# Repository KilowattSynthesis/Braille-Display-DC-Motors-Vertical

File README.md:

# Braille-Display-DC-Motors-Vertical

Braille display POC using 0408 DC motors, vertically inline under each dot, to spin a bolt for each dot. Includes CAD, PCB, and Firmware. 

**Type 5:** Vertical DC motors.

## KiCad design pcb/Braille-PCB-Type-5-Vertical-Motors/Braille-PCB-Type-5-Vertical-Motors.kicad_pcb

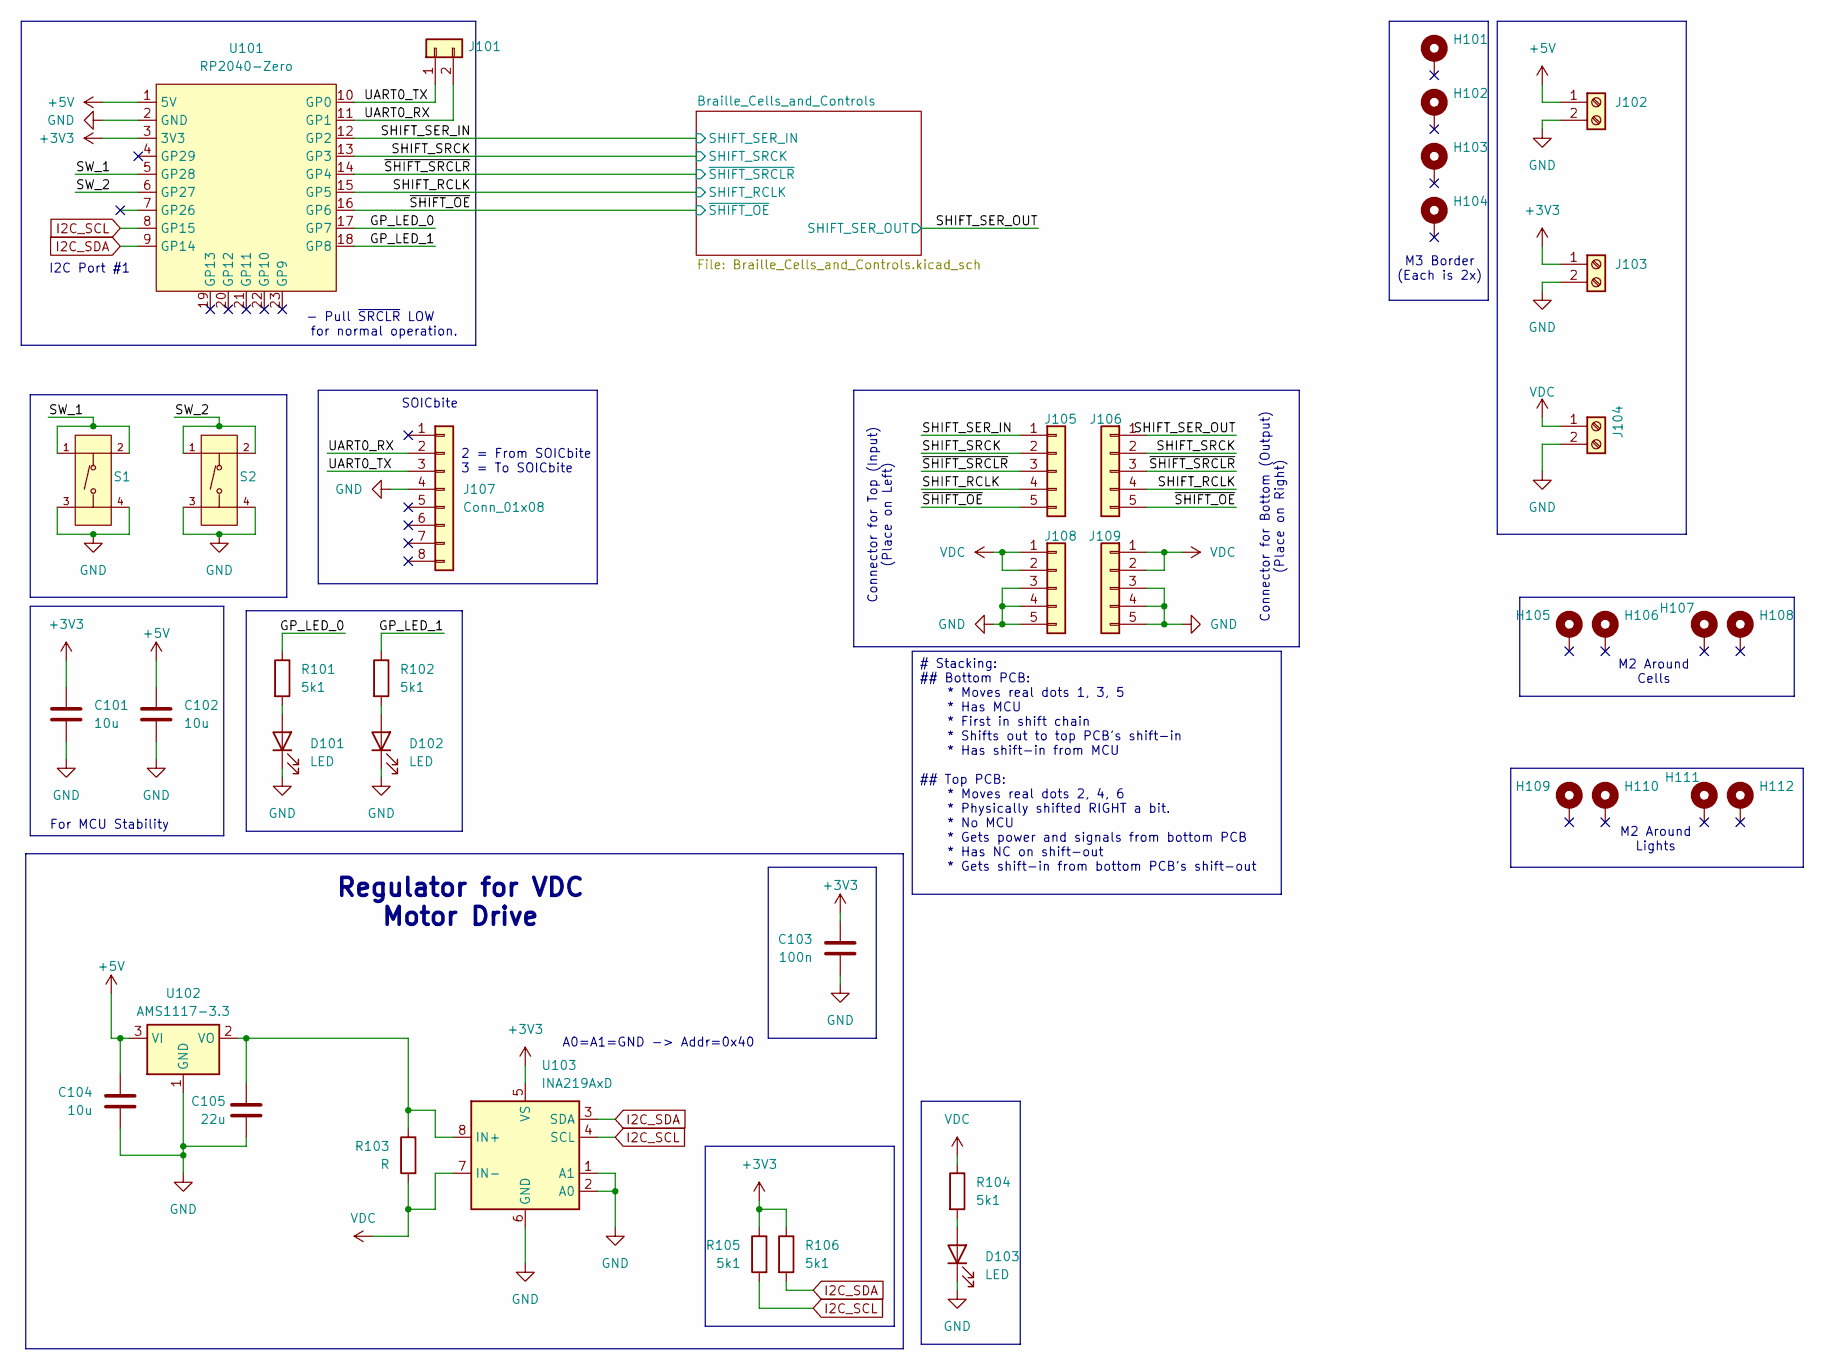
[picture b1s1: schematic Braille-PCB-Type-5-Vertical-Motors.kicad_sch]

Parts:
C101, C102, C104: 10u; C_1206_3216Metric_Pad1.33x1.80mm_HandSolder
C103: 100n; C_0603_1608Metric_Pad1.08x0.95mm_HandSolder
C105: 22u; C_1206_3216Metric_Pad1.33x1.80mm_HandSolder
D101, D102, D103: LED; LED_0603_1608Metric_Pad1.05x0.95mm_HandSolder
H101, H102, H103, H104: MountingHole_Pad; MountingHole_M3_2x_3mm_Pitch
H105, H106, H107, H108, H109, H110, H111, H112: MountingHole_Pad; Braille_Block_MountingHoles_M2_3x
J101: Conn_01x02; PinHeader_1x02_P2.54mm_Vertical
J102, J103, J104: Screw_Terminal_01x02; TerminalBlock_bornier-2_P5.08mm
J105, J106, J108, J109: Conn_01x05; PinHeader_1x05_P2.54mm_Vertical_Tight_Centered
J107: Conn_01x08; SOICbite_clipProgSmall
R101, R102, R104, R105, R106: 5k1; R_0603_1608Metric_Pad0.98x0.95mm_HandSolder
R103: R; R_1206_3216Metric_Pad1.30x1.75mm_HandSolder
S1, S2: Tactile Button, 160gf; SW-SMD_4P-L5.1-W5.1-P3.70-LS6.5-TL-2; Voltage Rating (Dc) 12V; Part TS-1187A-B-A-B; LCSC C318884
U101: RP2040-Zero; RP2040 Zero
U102: AMS1117-3.3; SOT-223-3_TabPin2
U103: INA219AxD; SOIC-8_3.9x4.9mm_P1.27mm

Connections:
+3V3: C101.1, C103.1, J103.1, R105.1, R106.1, U101.3 (3V3), U103.5 (VS); also elsewhere on the board
+5V: C102.1, C104.1, J102.1, U101.1 (5V), U102.3 (VI)
/GP_LED_0: R101.1, U101.17 (GP7)
/GP_LED_1: R102.1, U101.18 (GP8)
/SHIFT_RCLK: J105.4, J106.4, U101.15 (GP5); also elsewhere on the board
/SHIFT_SER_IN: J105.1, U101.12 (GP2); also elsewhere on the board
/SHIFT_SER_OUT: J106.1; also elsewhere on the board
/SHIFT_SRCK: J105.2, J106.2, U101.13 (GP3); also elsewhere on the board
/SW_1: S1.1 (A), S1.2 (B), U101.5 (GP28); also elsewhere on the board
/SW_2: S2.1 (A), S2.2 (B), U101.6 (GP27); also elsewhere on the board
/UART0_RX: J101.2, J107.2, U101.11 (GP1)
/UART0_TX: J101.1, J107.3, U101.10 (GP0)
/~SHIFT_OE: J105.5, J106.5, U101.16 (GP6); also elsewhere on the board
/~SHIFT_SRCLR: J105.3, J106.3, U101.14 (GP4); also elsewhere on the board
GND: C101.2, C102.2, C103.2, C104.2, C105.2, D101.1 (K), D102.1 (K), D103.1 (K), J102.2, J103.2, J104.2, J107.4, J108.3, J108.4, J108.5, J109.3, J109.4, J109.5, S1.3 (C), S1.4 (D), S2.3 (C), S2.4 (D), U101.2 (GND), U102.1 (GND), U103.1 (A1), U103.2 (A0), U103.6 (GND); also elsewhere on the board
I2C_SCL: R105.2, U101.8 (GP15), U103.4 (SCL)
I2C_SDA: R106.2, U101.9 (GP14), U103.3 (SDA)
unnamed: D101.2 (A), R101.2
unnamed: D102.2 (A), R102.2
unnamed: D103.2 (A), R104.2
unnamed: C105.1, R103.1, U102.2 (VO), U103.8 (IN+)
VDC: J104.1, J108.1, J108.2, J109.1, J109.2, R103.2, R104.1, U103.7 (IN-); also elsewhere on the board

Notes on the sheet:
SOICbite
2 = From SOICbite 3 = To SOICbite
M2 Around Cells
For MCU Stability
A0=A1=GND -> Addr=0x40
I2C Port #1
- Pull ~{SRCLR} LOW for normal operation.
M3 Border (Each is 2x)
M2 Around Lights
Connector for Top (Input) (Place on Left)
Connector for Bottom (Output) (Place on Right)
Regulator for VDC Motor Drive
# Stacking: ## Bottom PCB: * Moves real dots 1, 3, 5 * Has MCU * First in shift chain * Shifts out to top PCB's shift-in * Has shift-in from MCU ## Top PCB: * Moves real dots 2, 4, 6 * Physically shifted RIGHT a bit. * No MCU * Gets power and signals from bottom PCB * Has NC on shift-out * Gets shi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

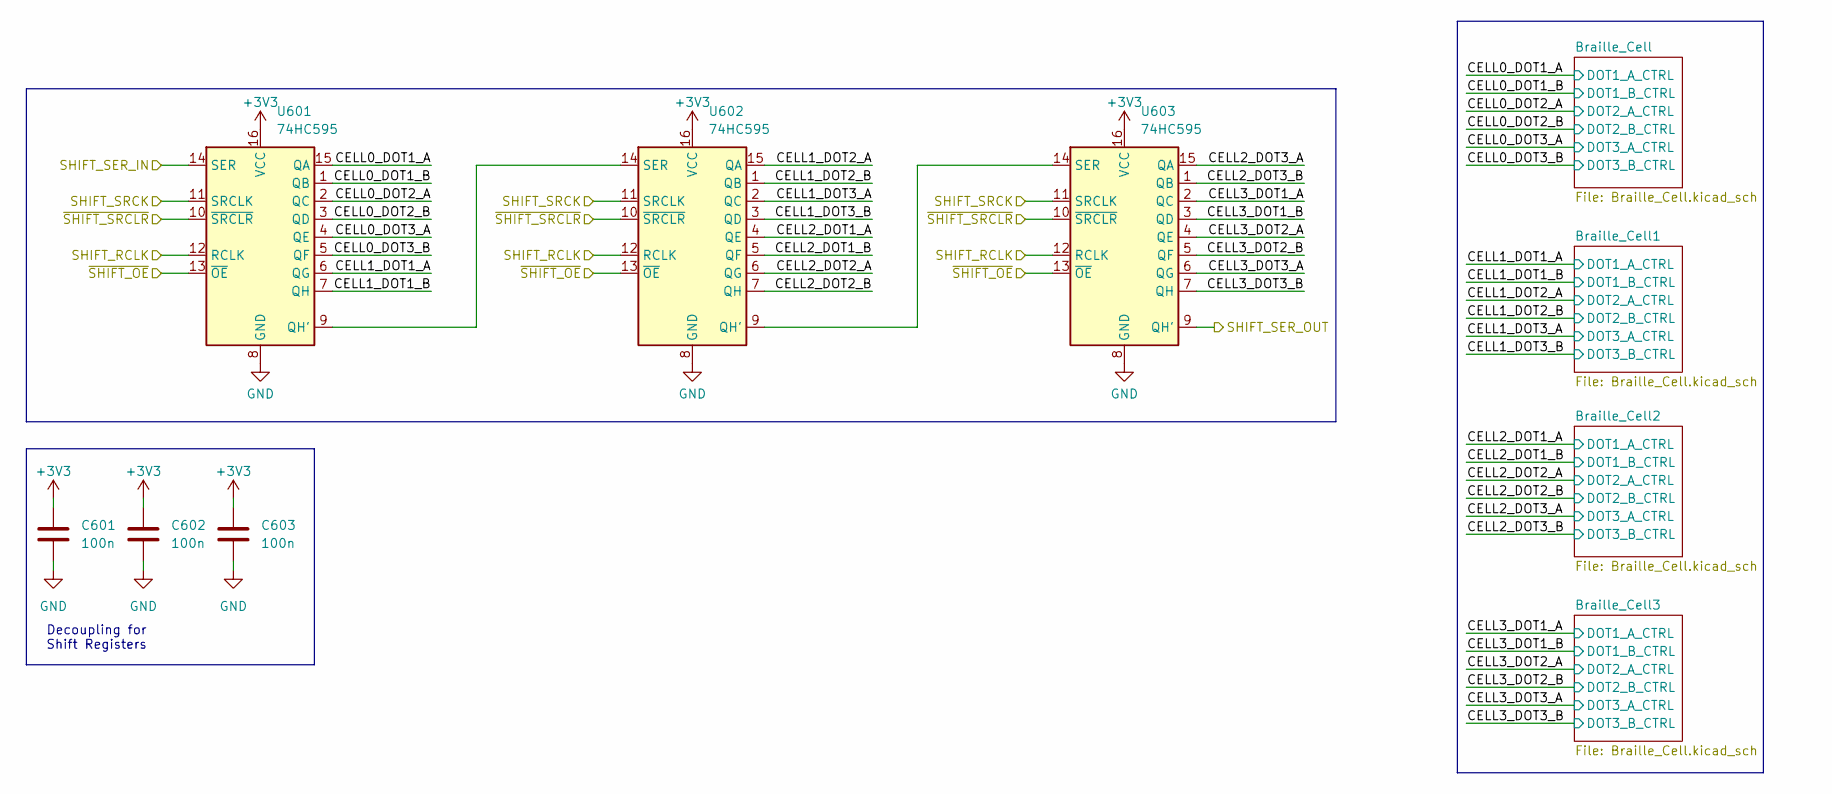
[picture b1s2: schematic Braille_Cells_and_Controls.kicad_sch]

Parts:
C601, C602, C603: 100n; C_0603_1608Metric_Pad1.08x0.95mm_HandSolder
U601, U602, U603: 74HC595; SOP-16_3.9x9.9mm_P1.27mm

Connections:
+3V3: C601.1, C602.1, C603.1, U601.16 (VCC), U602.16 (VCC), U603.16 (VCC); also elsewhere on the board
/Braille_Cells_and_Controls/CELL0_DOT1_A: U601.15 (QA); also elsewhere on the board
/Braille_Cells_and_Controls/CELL0_DOT1_B: U601.1 (QB); also elsewhere on the board
/Braille_Cells_and_Controls/CELL0_DOT2_A: U601.2 (QC); also elsewhere on the board
/Braille_Cells_and_Controls/CELL0_DOT2_B: U601.3 (QD); also elsewhere on the board
/Braille_Cells_and_Controls/CELL0_DOT3_A: U601.4 (QE); also elsewhere on the board
/Braille_Cells_and_Controls/CELL0_DOT3_B: U601.5 (QF); also elsewhere on the board
/Braille_Cells_and_Controls/CELL1_DOT1_A: U601.6 (QG); also elsewhere on the board
/Braille_Cells_and_Controls/CELL1_DOT1_B: U601.7 (QH); also elsewhere on the board
/Braille_Cells_and_Controls/CELL1_DOT2_A: U602.15 (QA); also elsewhere on the board
/Braille_Cells_and_Controls/CELL1_DOT2_B: U602.1 (QB); also elsewhere on the board
/Braille_Cells_and_Controls/CELL1_DOT3_A: U602.2 (QC); also elsewhere on the board
/Braille_Cells_and_Controls/CELL1_DOT3_B: U602.3 (QD); also elsewhere on the board
/Braille_Cells_and_Controls/CELL2_DOT1_A: U602.4 (QE); also elsewhere on the board
/Braille_Cells_and_Controls/CELL2_DOT1_B: U602.5 (QF); also elsewhere on the board
/Braille_Cells_and_Controls/CELL2_DOT2_A: U602.6 (QG); also elsewhere on the board
/Braille_Cells_and_Controls/CELL2_DOT2_B: U602.7 (QH); also elsewhere on the board
/Braille_Cells_and_Controls/CELL2_DOT3_A: U603.15 (QA); also elsewhere on the board
/Braille_Cells_and_Controls/CELL2_DOT3_B: U603.1 (QB); also elsewhere on the board
/Braille_Cells_and_Controls/CELL3_DOT1_A: U603.2 (QC); also elsewhere on the board
/Braille_Cells_and_Controls/CELL3_DOT1_B: U603.3 (QD); also elsewhere on the board
/Braille_Cells_and_Controls/CELL3_DOT2_A: U603.4 (QE); also elsewhere on the board
/Braille_Cells_and_Controls/CELL3_DOT2_B: U603.5 (QF); also elsewhere on the board
/Braille_Cells_and_Controls/CELL3_DOT3_A: U603.6 (QG); also elsewhere on the board
/Braille_Cells_and_Controls/CELL3_DOT3_B: U603.7 (QH); also elsewhere on the board
/SHIFT_RCLK: U601.12 (RCLK), U602.12 (RCLK), U603.12 (RCLK); also elsewhere on the board
/SHIFT_SER_IN: U601.14 (SER); also elsewhere on the board
/SHIFT_SER_OUT: U603.9 (QH'); also elsewhere on the board
/SHIFT_SRCK: U601.11 (SRCLK), U602.11 (SRCLK), U603.11 (SRCLK); also elsewhere on the board
/~SHIFT_OE: U601.13 (~OE), U602.13 (~OE), U603.13 (~OE); also elsewhere on the board
/~SHIFT_SRCLR: U601.10 (~SRCLR), U602.10 (~SRCLR), U603.10 (~SRCLR); also elsewhere on the board
GND: C601.2, C602.2, C603.2, U601.8 (GND), U602.8 (GND), U603.8 (GND); also elsewhere on the board
unnamed: U601.9 (QH'), U602.14 (SER)
unnamed: U602.9 (QH'), U603.14 (SER)

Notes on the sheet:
Decoupling for Shift Registers

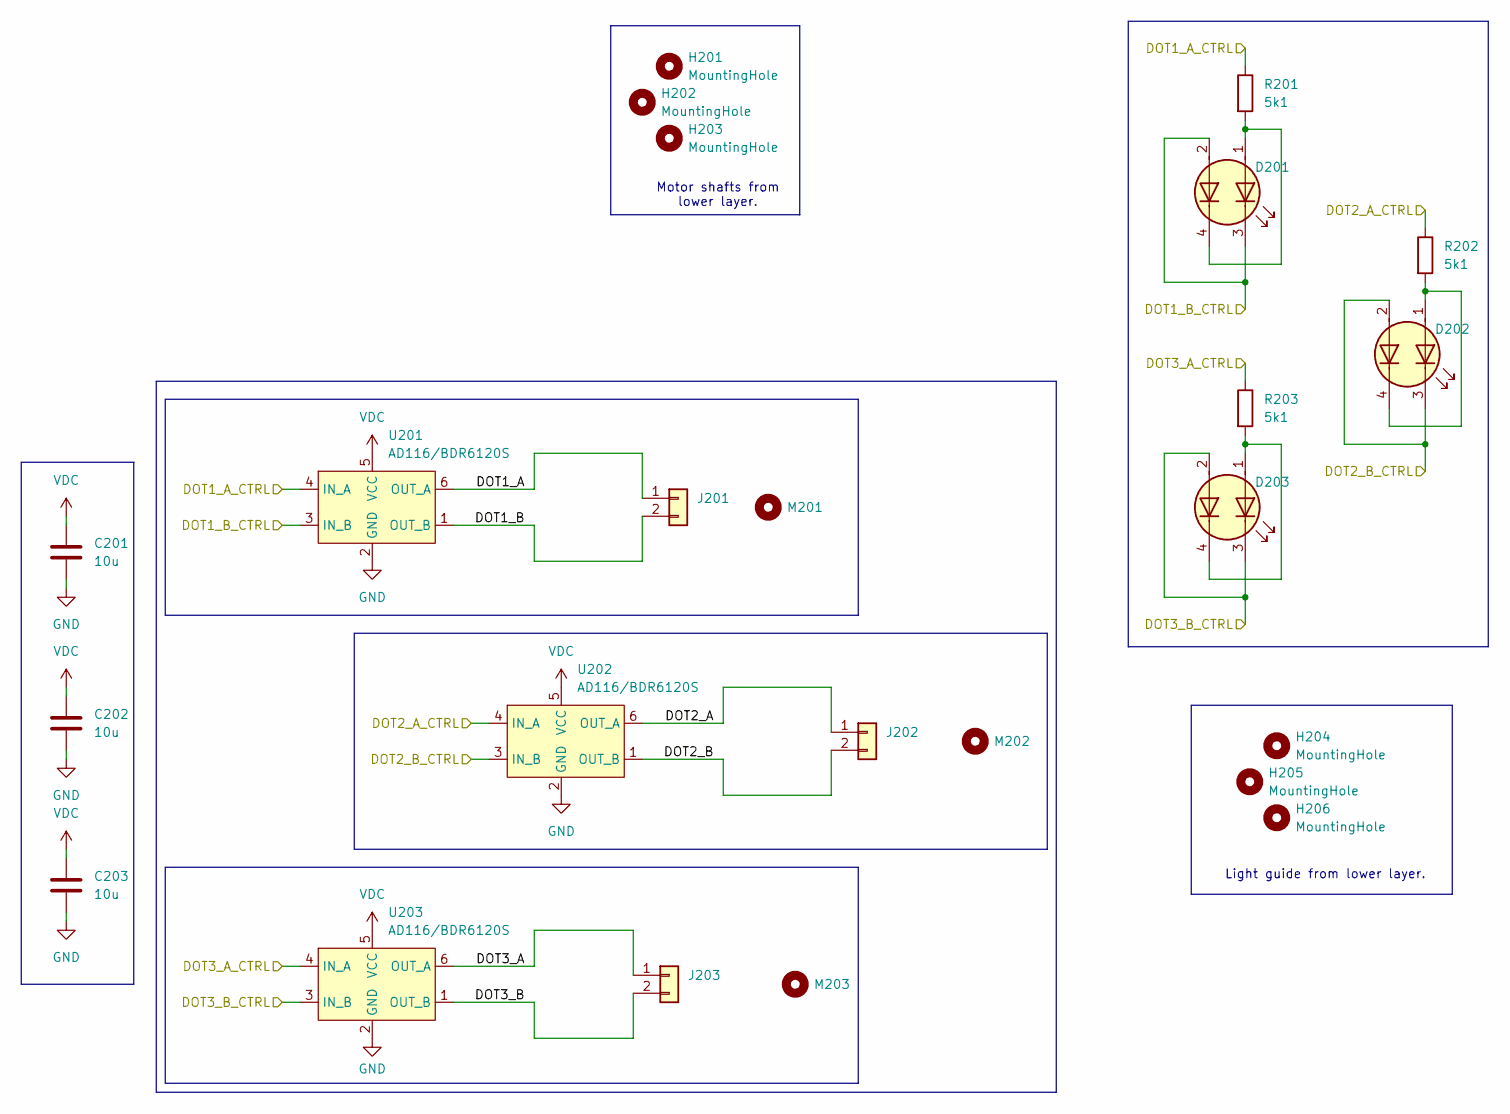
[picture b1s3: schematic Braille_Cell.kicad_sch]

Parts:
C201, C202, C203: 10u; C_1206_3216Metric_Pad1.33x1.80mm_HandSolder
D201, D202, D203: LED_Dual_AAKK; LED_1206_Bicolor_AAKK
H201, H202, H203, H204, H205, H206: MountingHole; Hole_for_Motor_Shaft
J201, J202, J203: Conn_01x02; PinHeader_1x02_P2.54mm_Vertical_Tight_Centered
M201, M202, M203: MountingHole; Motor_Tiny_0408_Vertical
R201, R202, R203: 5k1; R_0603_1608Metric_Pad0.98x0.95mm_HandSolder
U201, U202, U203: AD116/BDR6120S; SOT-23-6

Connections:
/Braille_Cells_and_Controls/Braille_Cell/DOT1_A: J201.1, U201.6 (OUT_A)
/Braille_Cells_and_Controls/Braille_Cell/DOT1_B: J201.2, U201.1 (OUT_B)
/Braille_Cells_and_Controls/Braille_Cell/DOT2_A: J202.1, U202.6 (OUT_A)
/Braille_Cells_and_Controls/Braille_Cell/DOT2_B: J202.2, U202.1 (OUT_B)
/Braille_Cells_and_Controls/Braille_Cell/DOT3_A: J203.1, U203.6 (OUT_A)
/Braille_Cells_and_Controls/Braille_Cell/DOT3_B: J203.2, U203.1 (OUT_B)
/Braille_Cells_and_Controls/CELL0_DOT1_A: R201.1, U201.4 (IN_A); also elsewhere on the board
/Braille_Cells_and_Controls/CELL0_DOT1_B: D201.2 (A2), D201.3 (K1), U201.3 (IN_B); also elsewhere on the board
/Braille_Cells_and_Controls/CELL0_DOT2_A: R202.1, U202.4 (IN_A); also elsewhere on the board
/Braille_Cells_and_Controls/CELL0_DOT2_B: D202.2 (A2), D202.3 (K1), U202.3 (IN_B); also elsewhere on the board
/Braille_Cells_and_Controls/CELL0_DOT3_A: R203.1, U203.4 (IN_A); also elsewhere on the board
/Braille_Cells_and_Controls/CELL0_DOT3_B: D203.2 (A2), D203.3 (K1), U203.3 (IN_B); also elsewhere on the board
GND: C201.2, C202.2, C203.2, U201.2 (GND), U202.2 (GND), U203.2 (GND); also elsewhere on the board
unnamed: D201.1 (A1), D201.4 (K2), R201.2
unnamed: D202.1 (A1), D202.4 (K2), R202.2
unnamed: D203.1 (A1), D203.4 (K2), R203.2
VDC: C201.1, C202.1, C203.1, U201.5 (VCC), U202.5 (VCC), U203.5 (VCC); also elsewhere on the board

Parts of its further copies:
C301, C302, C303, C401, C402, C403, C501, C502, C503: 10u; C_1206_3216Metric_Pad1.33x1.80mm_HandSolder
D301, D302, D303, D401, D402, D403, D501, D502, D503: LED_Dual_AAKK; LED_1206_Bicolor_AAKK
H301, H302, H303, H304, H305, H306, H401, H402, H403, H404, H405, H406, H501, H502, H503, H504, H505, H506: MountingHole; Hole_for_Motor_Shaft
J301, J302, J303, J401, J402, J403, J501, J502, J503: Conn_01x02; PinHeader_1x02_P2.54mm_Vertical_Tight_Centered
M301, M302, M303, M401, M402, M403, M501, M502, M503: MountingHole; Motor_Tiny_0408_Vertical
R301, R302, R303, R401, R402, R403, R501, R502, R503: 5k1; R_0603_1608Metric_Pad0.98x0.95mm_HandSolder

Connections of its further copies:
/Braille_Cells_and_Controls/Braille_Cell1/DOT1_A: J301.1; also elsewhere on the board
/Braille_Cells_and_Controls/Braille_Cell1/DOT1_B: J301.2; also elsewhere on the board
/Braille_Cells_and_Controls/Braille_Cell1/DOT2_A: J302.1; also elsewhere on the board
/Braille_Cells_and_Controls/Braille_Cell1/DOT2_B: J302.2; also elsewhere on the board
/Braille_Cells_and_Controls/Braille_Cell1/DOT3_A: J303.1; also elsewhere on the board
/Braille_Cells_and_Controls/Braille_Cell1/DOT3_B: J303.2; also elsewhere on the board
/Braille_Cells_and_Controls/Braille_Cell2/DOT1_A: J401.1; also elsewhere on the board
/Braille_Cells_and_Controls/Braille_Cell2/DOT1_B: J401.2; also elsewhere on the board
/Braille_Cells_and_Controls/Braille_Cell2/DOT2_A: J402.1; also elsewhere on the board
/Braille_Cells_and_Controls/Braille_Cell2/DOT2_B: J402.2; also elsewhere on the board
/Braille_Cells_and_Controls/Braille_Cell2/DOT3_A: J403.1; also elsewhere on the board
/Braille_Cells_and_Controls/Braille_Cell2/DOT3_B: J403.2; also elsewhere on the board
/Braille_Cells_and_Controls/Braille_Cell3/DOT1_A: J501.1; also elsewhere on the board
/Braille_Cells_and_Controls/Braille_Cell3/DOT1_B: J501.2; also elsewhere on the board
/Braille_Cells_and_Controls/Braille_Cell3/DOT2_A: J502.1; also elsewhere on the board
/Braille_Cells_and_Controls/Braille_Cell3/DOT2_B: J502.2; also elsewhere on the board
/Braille_Cells_and_Controls/Braille_Cell3/DOT3_A: J503.1; also elsewhere on the board
/Braille_Cells_and_Controls/Braille_Cell3/DOT3_B: J503.2; also elsewhere on the board
/Braille_Cells_and_Controls/CELL1_DOT1_A: R301.1; also elsewhere on the board
/Braille_Cells_and_Controls/CELL1_DOT1_B: D301.2 (A2), D301.3 (K1); also elsewhere on the board
/Braille_Cells_and_Controls/CELL1_DOT2_A: R302.1; also elsewhere on the board
/Braille_Cells_and_Controls/CELL1_DOT2_B: D302.2 (A2), D302.3 (K1); also elsewhere on the board
/Braille_Cells_and_Controls/CELL1_DOT3_A: R303.1; also elsewhere on the board
/Braille_Cells_and_Controls/CELL1_DOT3_B: D303.2 (A2), D303.3 (K1); also elsewhere on the board
/Braille_Cells_and_Controls/CELL2_DOT1_A: R401.1; also elsewhere on the board
/Braille_Cells_and_Controls/CELL2_DOT1_B: D401.2 (A2), D401.3 (K1); also elsewhere on the board
/Braille_Cells_and_Controls/CELL2_DOT2_A: R402.1; also elsewhere on the board
/Braille_Cells_and_Controls/CELL2_DOT2_B: D402.2 (A2), D402.3 (K1); also elsewhere on the board
/Braille_Cells_and_Controls/CELL2_DOT3_A: R403.1; also elsewhere on the board
/Braille_Cells_and_Controls/CELL2_DOT3_B: D403.2 (A2), D403.3 (K1); also elsewhere on the board
/Braille_Cells_and_Controls/CELL3_DOT1_A: R501.1; also elsewhere on the board
/Braille_Cells_and_Controls/CELL3_DOT1_B: D501.2 (A2), D501.3 (K1); also elsewhere on the board
/Braille_Cells_and_Controls/CELL3_DOT2_A: R502.1; also elsewhere on the board
/Braille_Cells_and_Controls/CELL3_DOT2_B: D502.2 (A2), D502.3 (K1); also elsewhere on the board
/Braille_Cells_and_Controls/CELL3_DOT3_A: R503.1; also elsewhere on the board
/Braille_Cells_and_Controls/CELL3_DOT3_B: D503.2 (A2), D503.3 (K1); also elsewhere on the board
GND: C301.2, C302.2, C303.2, C401.2, C402.2, C403.2, C501.2, C502.2, C503.2; also elsewhere on the board
unnamed: D301.1 (A1), D301.4 (K2), R301.2
unnamed: D302.1 (A1), D302.4 (K2), R302.2
unnamed: D303.1 (A1), D303.4 (K2), R303.2
unnamed: D401.1 (A1), D401.4 (K2), R401.2
unnamed: D402.1 (A1), D402.4 (K2), R402.2
unnamed: D403.1 (A1), D403.4 (K2), R403.2
unnamed: D501.1 (A1), D501.4 (K2), R501.2
unnamed: D502.1 (A1), D502.4 (K2), R502.2
unnamed: D503.1 (A1), D503.4 (K2), R503.2
VDC: C301.1, C302.1, C303.1, C401.1, C402.1, C403.1, C501.1, C502.1, C503.1; also elsewhere on the board

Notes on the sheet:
Light guide from lower layer.
Motor shafts from lower layer.

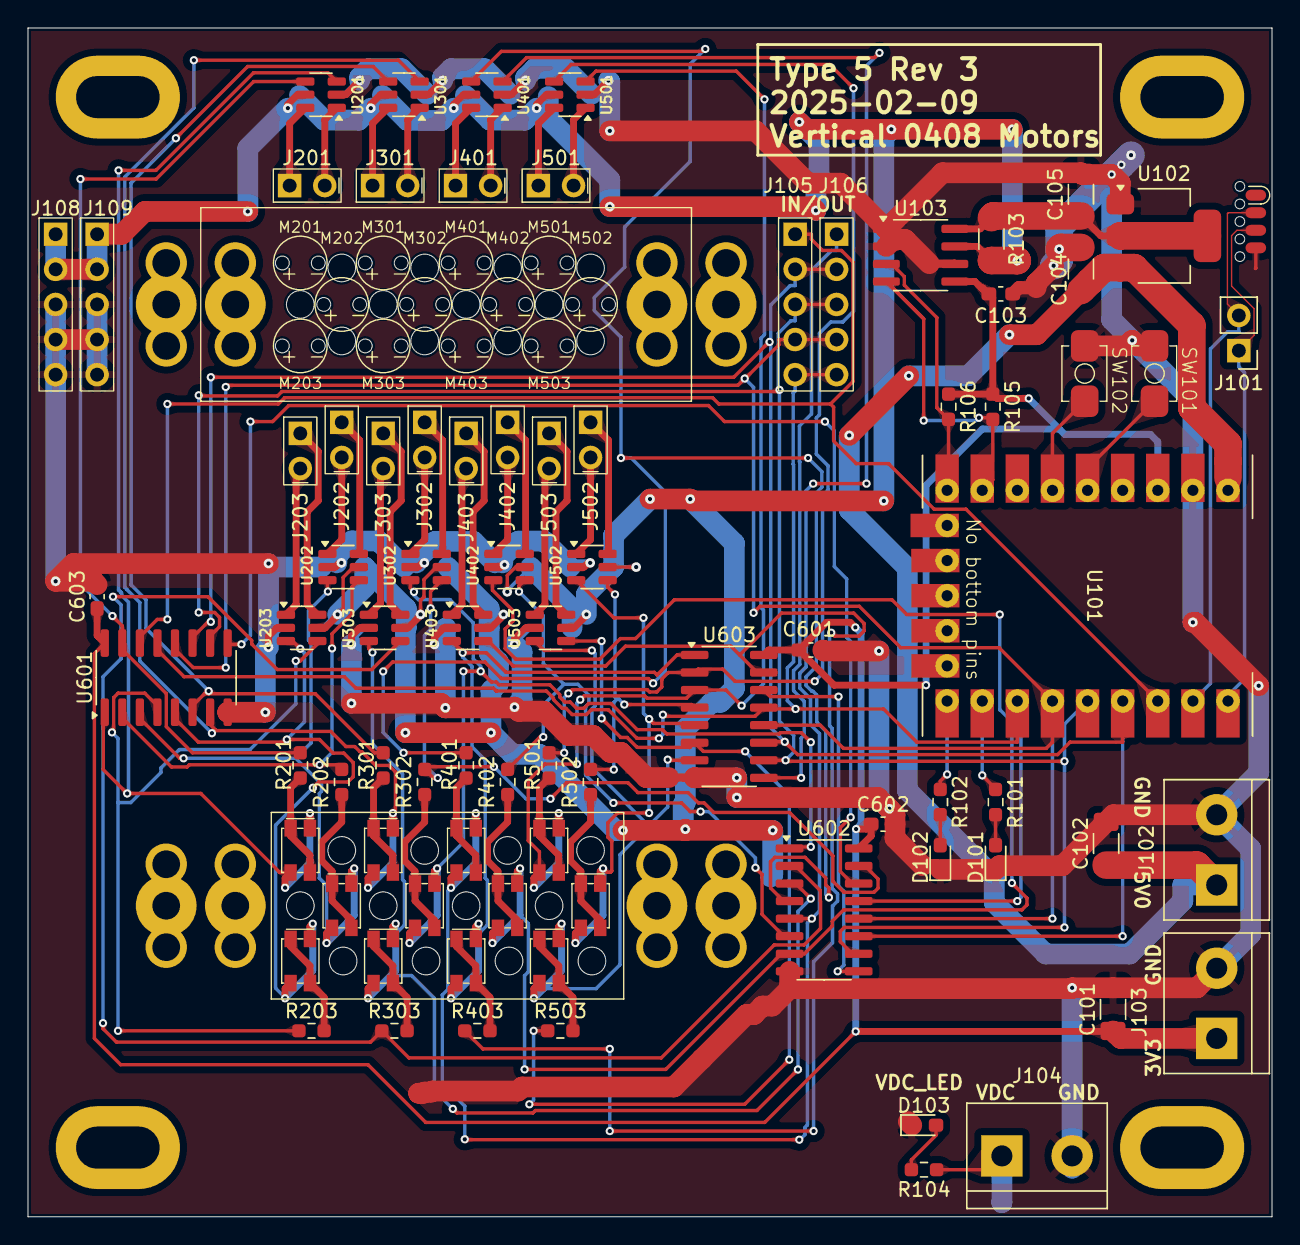
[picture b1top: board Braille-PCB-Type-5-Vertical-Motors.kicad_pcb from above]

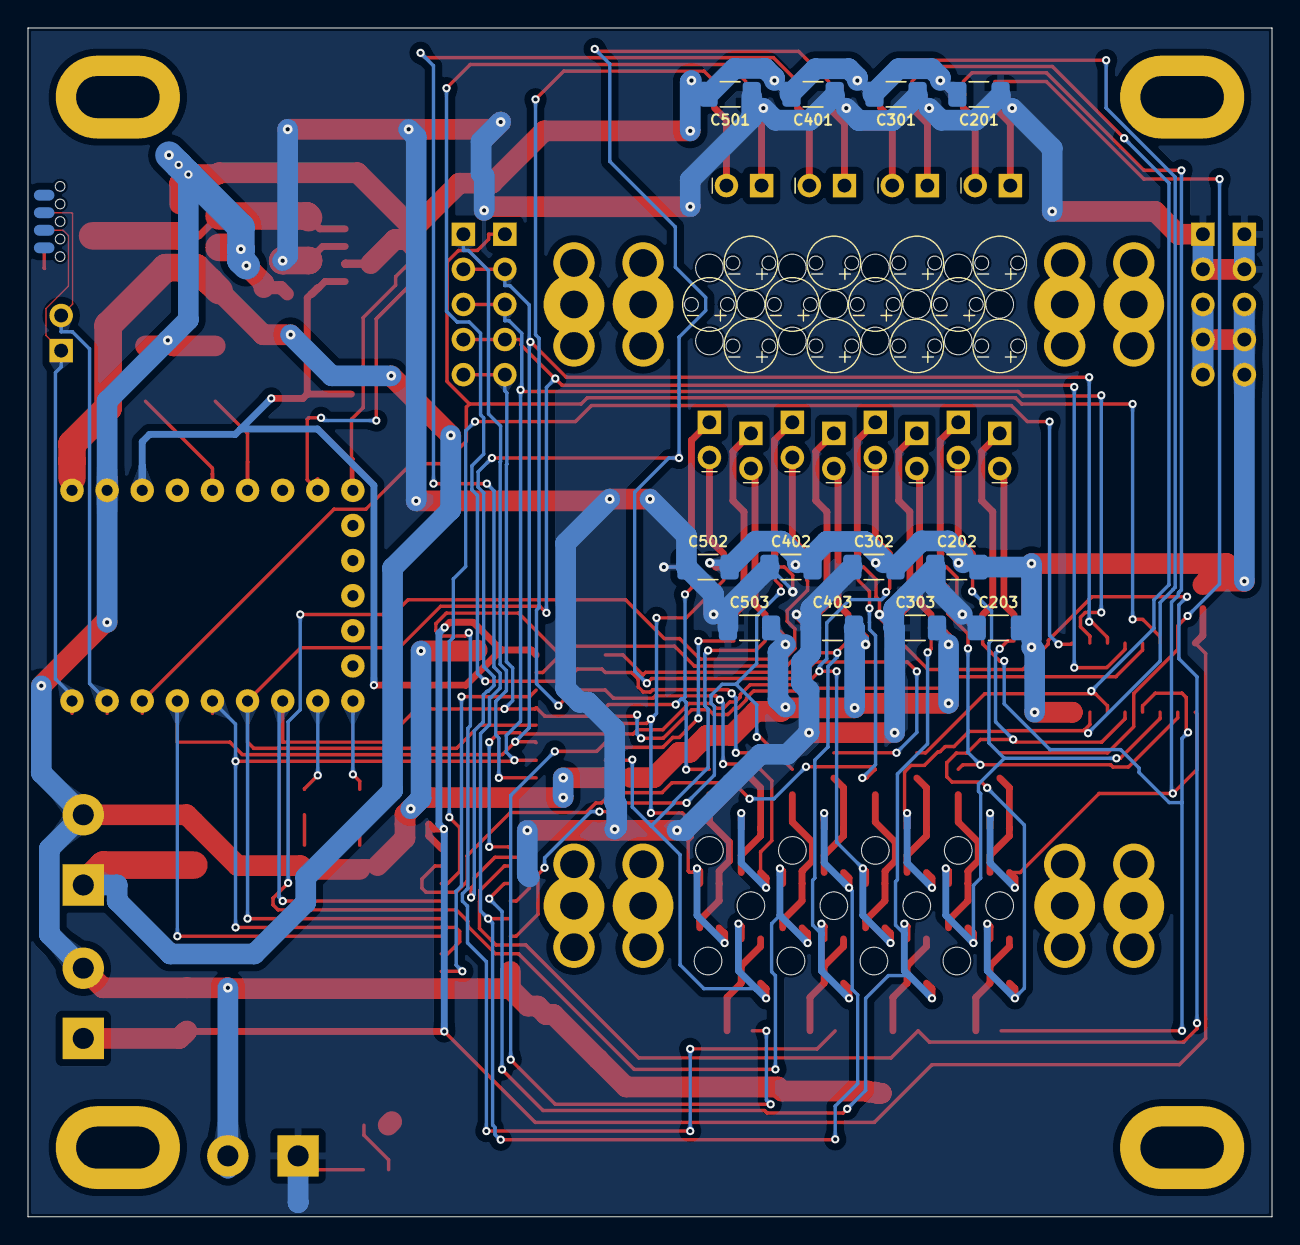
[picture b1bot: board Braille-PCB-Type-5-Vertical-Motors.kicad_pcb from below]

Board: 2 copper layers, 90.0 x 86.0 mm, 142 parts (12 on the bottom side), 84 nets.

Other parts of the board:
SW101, SW102: SW_Push; PushButtonSMD_2.93x3.9
U301, U302, U303, U401, U402, U403, U501, U502, U503: AD116; SOT-23-6

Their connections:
/Braille_Cells_and_Controls/Braille_Cell1/DOT1_A: U301.6 (OUT_A); also elsewhere on the board
/Braille_Cells_and_Controls/Braille_Cell1/DOT1_B: U301.1 (OUT_B); also elsewhere on the board
/Braille_Cells_and_Controls/Braille_Cell1/DOT2_A: U302.6 (OUT_A); also elsewhere on the board
/Braille_Cells_and_Controls/Braille_Cell1/DOT2_B: U302.1 (OUT_B); also elsewhere on the board
/Braille_Cells_and_Controls/Braille_Cell1/DOT3_A: U303.6 (OUT_A); also elsewhere on the board
/Braille_Cells_and_Controls/Braille_Cell1/DOT3_B: U303.1 (OUT_B); also elsewhere on the board
/Braille_Cells_and_Controls/Braille_Cell2/DOT1_A: U401.6 (OUT_A); also elsewhere on the board
/Braille_Cells_and_Controls/Braille_Cell2/DOT1_B: U401.1 (OUT_B); also elsewhere on the board
/Braille_Cells_and_Controls/Braille_Cell2/DOT2_A: U402.6 (OUT_A); also elsewhere on the board
/Braille_Cells_and_Controls/Braille_Cell2/DOT2_B: U402.1 (OUT_B); also elsewhere on the board
/Braille_Cells_and_Controls/Braille_Cell2/DOT3_A: U403.6 (OUT_A); also elsewhere on the board
/Braille_Cells_and_Controls/Braille_Cell2/DOT3_B: U403.1 (OUT_B); also elsewhere on the board
/Braille_Cells_and_Controls/Braille_Cell3/DOT1_A: U501.6 (OUT_A); also elsewhere on the board
/Braille_Cells_and_Controls/Braille_Cell3/DOT1_B: U501.1 (OUT_B); also elsewhere on the board
/Braille_Cells_and_Controls/Braille_Cell3/DOT2_A: U502.6 (OUT_A); also elsewhere on the board
/Braille_Cells_and_Controls/Braille_Cell3/DOT2_B: U502.1 (OUT_B); also elsewhere on the board
/Braille_Cells_and_Controls/Braille_Cell3/DOT3_A: U503.6 (OUT_A); also elsewhere on the board
/Braille_Cells_and_Controls/Braille_Cell3/DOT3_B: U503.1 (OUT_B); also elsewhere on the board
/Braille_Cells_and_Controls/CELL1_DOT1_A: U301.4 (IN_A); also elsewhere on the board
/Braille_Cells_and_Controls/CELL1_DOT1_B: U301.3 (IN_B); also elsewhere on the board
/Braille_Cells_and_Controls/CELL1_DOT2_A: U302.4 (IN_A); also elsewhere on the board
/Braille_Cells_and_Controls/CELL1_DOT2_B: U302.3 (IN_B); also elsewhere on the board
/Braille_Cells_and_Controls/CELL1_DOT3_A: U303.4 (IN_A); also elsewhere on the board
/Braille_Cells_and_Controls/CELL1_DOT3_B: U303.3 (IN_B); also elsewhere on the board
/Braille_Cells_and_Controls/CELL2_DOT1_A: U401.4 (IN_A); also elsewhere on the board
/Braille_Cells_and_Controls/CELL2_DOT1_B: U401.3 (IN_B); also elsewhere on the board
/Braille_Cells_and_Controls/CELL2_DOT2_A: U402.4 (IN_A); also elsewhere on the board
/Braille_Cells_and_Controls/CELL2_DOT2_B: U402.3 (IN_B); also elsewhere on the board
/Braille_Cells_and_Controls/CELL2_DOT3_A: U403.4 (IN_A); also elsewhere on the board
/Braille_Cells_and_Controls/CELL2_DOT3_B: U403.3 (IN_B); also elsewhere on the board
/Braille_Cells_and_Controls/CELL3_DOT1_A: U501.4 (IN_A); also elsewhere on the board
/Braille_Cells_and_Controls/CELL3_DOT1_B: U501.3 (IN_B); also elsewhere on the board
/Braille_Cells_and_Controls/CELL3_DOT2_A: U502.4 (IN_A); also elsewhere on the board
/Braille_Cells_and_Controls/CELL3_DOT2_B: U502.3 (IN_B); also elsewhere on the board
/Braille_Cells_and_Controls/CELL3_DOT3_A: U503.4 (IN_A); also elsewhere on the board
/Braille_Cells_and_Controls/CELL3_DOT3_B: U503.3 (IN_B); also elsewhere on the board
/SW_1: SW101.2; also elsewhere on the board
/SW_2: SW102.2; also elsewhere on the board
GND: SW101.1, SW102.1, U301.2 (GND), U302.2 (GND), U303.2 (GND), U401.2 (GND), U402.2 (GND), U403.2 (GND), U501.2 (GND), U502.2 (GND), U503.2 (GND); also elsewhere on the board
VDC: U301.5 (VCC), U302.5 (VCC), U303.5 (VCC), U401.5 (VCC), U402.5 (VCC), U403.5 (VCC), U501.5 (VCC), U502.5 (VCC), U503.5 (VCC); also elsewhere on the board

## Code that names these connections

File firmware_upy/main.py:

from machine import Pin
import time

# Sleep a bit longer in init to ensure it gets set right.
SHIFT_REGISTER_INIT_SLEEP_MS = 100

# Sleep time between each bit shift.
SHIFT_REGISTER_SLEEP_US = 2000

# Pin definitions for shift register control
PIN_SHIFT_SER_IN = Pin(2, Pin.OUT)  # GP2: Serial data input
PIN_SHIFT_SRCK = Pin(3, Pin.OUT)  # GP3: Shift register clock
PIN_SHIFT_N_SRCLR = Pin(4, Pin.OUT)  # GP4: Shift register clear
PIN_SHIFT_RCLK = Pin(5, Pin.OUT)  # GP5: Register clock (latch)
PIN_SHIFT_N_OE = Pin(6, Pin.OUT)  # GP6: Output enable

PIN_SW1 = Pin(28, Pin.IN, Pin.PULL_UP)
PIN_SW2 = Pin(27, Pin.IN, Pin.PULL_UP)
PIN_GP_LED_0 = Pin(7, Pin.OUT)
PIN_GP_LED_1 = Pin(8, Pin.OUT)


def init_shift_register() -> None:
    """Initialize shift register pins to default states."""
    # Clear shift register.
    PIN_SHIFT_N_SRCLR.value(0)
    time.sleep_ms(SHIFT_REGISTER_INIT_SLEEP_MS)
    PIN_SHIFT_N_SRCLR.value(1)  # Active low, so set to normal (not clearing).
    time.sleep_ms(SHIFT_REGISTER_INIT_SLEEP_MS)

    PIN_SHIFT_N_OE.value(0)  # Active low, set low to enable outputs
    PIN_SHIFT_SRCK.value(0)  # Clock starts low
    PIN_SHIFT_RCLK.value(0)  # Latch starts low

    # Wait for initialization to complete
    time.sleep_ms(SHIFT_REGISTER_INIT_SLEEP_MS)

    # Clear all outputs.
    set_shift_registers([False] * 48)
    time.sleep_ms(SHIFT_REGISTER_INIT_SLEEP_MS)


def set_shift_registers(data: list[bool]) -> None:
    """
    Set the state of all shift registers based on input data.

    Args:
        data: list of 48 boolean values representing desired output states
             (6 registers x 8 bits per register)
    """
    if len(data) != 48:
        raise ValueError("Data must contain exactly 48 boolean values")

    # Shift out all 48 bits
    for bit in reversed(data):  # Shift MSB first
        # Set data bit.
        PIN_SHIFT_SER_IN.value(1 if bit else 0)
        time.sleep_us(SHIFT_REGISTER_SLEEP_US)

        # Clock in the bit.
        PIN_SHIFT_SRCK.value(1)
        time.sleep_us(SHIFT_REGISTER_SLEEP_US)
        PIN_SHIFT_SRCK.value(0)
        time.sleep_us(SHIFT_REGISTER_SLEEP_US)

    # Latch the data to outputs
    PIN_SHIFT_RCLK.value(1)
    time.sleep_us(SHIFT_REGISTER_SLEEP_US)
    PIN_SHIFT_RCLK.value(0)
    time.sleep_us(SHIFT_REGISTER_SLEEP_US)


def basic_demo() -> None:
    print("All outputs off (high-impedance)")
    outputs = [False] * 48  # All outputs off
    set_shift_registers(outputs)
    time.sleep(2)

    print("All outputs on - positive")
    outputs = [(i % 2 == 0) for i in range(48)]  # Alternating on/off pattern
    set_shift_registers(outputs)
    time.sleep(2)

    print("All outputs on - negative")
    outputs = [(i % 2 == 1) for i in range(48)]  # Alternating on/off pattern
    set_shift_registers(outputs)
    time.sleep(2)

def make_shift_register_list_of_cells(
    cell_states: list[tuple[str, str, str, str, str, str] | str],
) -> list[bool]:
    """Convert a list of cell states to a list of shift register states."""
    shift_register_state = [False] * 48

    for cell_number, cell_state in enumerate(cell_states):
        if isinstance(cell_state, str):
            cell_state = (
                cell_state,
                cell_state,
                cell_state,
                cell_state,
                cell_state,
                cell_state,
            )

        for dot_number, state in enumerate(cell_state):
            base_offset = cell_number * 6 * 2 + dot_number * 2
            in_a_in_b = {
                "brake": (True, True),
                "high-z": (False, False),
                "pos": (True, False),
                "neg": (False, True),
            }[state]
            shift_register_state[base_offset] = in_a_in_b[0]
            shift_register_state[base_offset + 1] = in_a_in_b[1]

    return shift_register_state


def respond_to_buttons() -> None:
    """Respond to the button presses by setting the state of all.
    
    * Pressing SW1 sets all to "pos" for a short time, then back to high-z.
    * Pressing SW2 sets all to "neg" for a short time, then back to high-z.
    """

    ACTION_TIME_MS = 250
    DEBOUNCE_TIME_MS = 400

    if PIN_SW1.value() == 0:
        print(f"SW1 pressed. Activate all for {ACTION_TIME_MS} ms.")
        PIN_GP_LED_0.value(1)
        direction = "pos"

    elif PIN_SW2.value() == 0:
        print(f"SW2 pressed. Activate all for {ACTION_TIME_MS} ms.")
        PIN_GP_LED_1.value(1)
        direction = "neg"

    else:
        return

    register_state = make_shift_register_list_of_cells([direction] * 4)
    # print(f"Setting shift registers: {register_state}")
    set_shift_registers(register_state)
    time.sleep_ms(ACTION_TIME_MS)
    set_shift_registers(make_shift_register_list_of_cells(["high-z"] * 4))
    print("Waiting for debounce.")
    time.sleep_ms(DEBOUNCE_TIME_MS)
    PIN_GP_LED_0.value(0)
    PIN_GP_LED_1.value(0)

def demo_each_dot_one_by_one() -> None:
    for dot_num in range(24):
        print(f"Dot {dot_num} - Direction 1")
        shift_register_state = [False] * 48
        shift_register_state[dot_num] = True
        set_shift_registers(shift_register_state)
        time.sleep(1)

        print(f"Dot {dot_num} - Direction 2")
        shift_register_state = [False] * 48
        shift_register_state[dot_num + 1] = True
        set_shift_registers(shift_register_state)
        time.sleep(1)


def main() -> None:
    print("Starting init.")
    init_shift_register()
    PIN_GP_LED_0.value(0)
    PIN_GP_LED_1.value(0)
    print("Init complete.")

    while 0:
        print("Starting basic demo.")
        basic_demo()
        print("Basic demo complete.")


    while 1:
        print("Starting demo_each_dot_one_by_one().")
        demo_each_dot_one_by_one()

    print("Starting respond_to_buttons().")
    while 1:
        respond_to_buttons()


while True:
    main()

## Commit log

2025-01-10 Migrate cad from `Braille-Display-CAD` repo
2025-01-10 Update action
2025-01-10 Fix missing docstring
2025-01-10 Migrate cad from `Braille-Display-CAD` repo (#1)
2025-01-10 Migrate PCB from `Braille-Display-Inductors-CAD` repo, `pcb-type-2-rev-2`
2025-01-10 Migrate PCB from `Braille-Display-Inductors-CAD` repo, `pcb-type-2-rev-2` (#2)
2025-01-10 PCB: Update to have 3 motors, dimensioned layout template
2025-01-10 PCB WIP: Add motor shaft holes
2025-01-10 PCB WIP: More layout
2025-01-10 PCB: Add cross-PCB connectors
2025-01-11 PCB: Finish setting up power planes
2025-01-11 Finish Type 5 Rev 1 PCB
2025-01-11 Add render to README
2025-01-11 PCB Rev 2: Increase shaft hole diameter from 1mm to 2mm
2025-02-03 pcb: in schematic, place motors closer to drivers
2025-02-03 Add testing firmware (migrated from inductor repo)
2025-02-03 Fix bad Python dependency
2025-02-04 cad: simplify housing, adapt for 2-PCB design
2025-02-08 PCB: Work on new revision
2025-02-08 More revision work
2025-02-08 Finish Rev 3
2025-02-24 cad: Bump versions
2025-02-24 cad: Add pegs for mounting holes
2025-02-24 cad: Increase motor OD to 4.5mm
2025-02-24 pcb: Bump to KiCAD v9
2025-02-25 cad: Add mounting holes above pegs back
2025-03-01 pcb: Add I2C address comments
2025-03-01 firmware: Add I2C current sensor code
2025-03-03 pcb: Motor driver model schematic comment
2025-03-03 cad: Add bushing_between_pcbs
2025-03-03 firmware: Add single-dot code demos
2025-03-03 cad: Create motor-to-spacer bushing
2025-03-03 cad: Add a bit extra to the bushings
2025-03-04 firmware: Add CLI prompt for testing
2025-03-05 cad: increase gap_above_top_motor
2025-03-06 firmware: Improve shift init time
2025-03-06 firmware: Add `self_test_each_dot` function
2025-03-06 firmware: Improve CLI UX
2025-03-12 firmware: Faster init, better debugging commands
2025-03-13 cad: Add dot-to-motor offset calculator
2025-03-16 cad: WIP - create slightly-offset cam concept
2025-03-16 cad: Add comment about motor-to-plate spacing
2025-03-18 cad: Finish prototype screw/ramp cams
2025-03-18 cad: create the top plate parts
2025-03-18 Create printable versions of the cams
2025-06-30 chore: bump KiCAD to v9, maybe other minor changes
2025-08-30 cad: migrate to uv
2025-08-30 cad: migrate to uv (#3)
2025-08-31 cad(hex_driver): create POC hex driver design
2025-08-31 cad(hex_driver): upgrade for metal printing POC
2025-08-31 cad(hex_driver): upgrade for metal printing POC (attempt 2)
2025-08-31 cad(hex_driver): add CNC machined variant
